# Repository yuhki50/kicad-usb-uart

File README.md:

# USB UART

## Board specifications

* Layer: 2
* Dimensions: 43.5 x 28.5 mm
* PCB Thickness: 1.0 mm
* PCB Color: Green
* Surface Finish: HASL Lead Free
* Castellated Hole: No
* Copper Weight:1oz

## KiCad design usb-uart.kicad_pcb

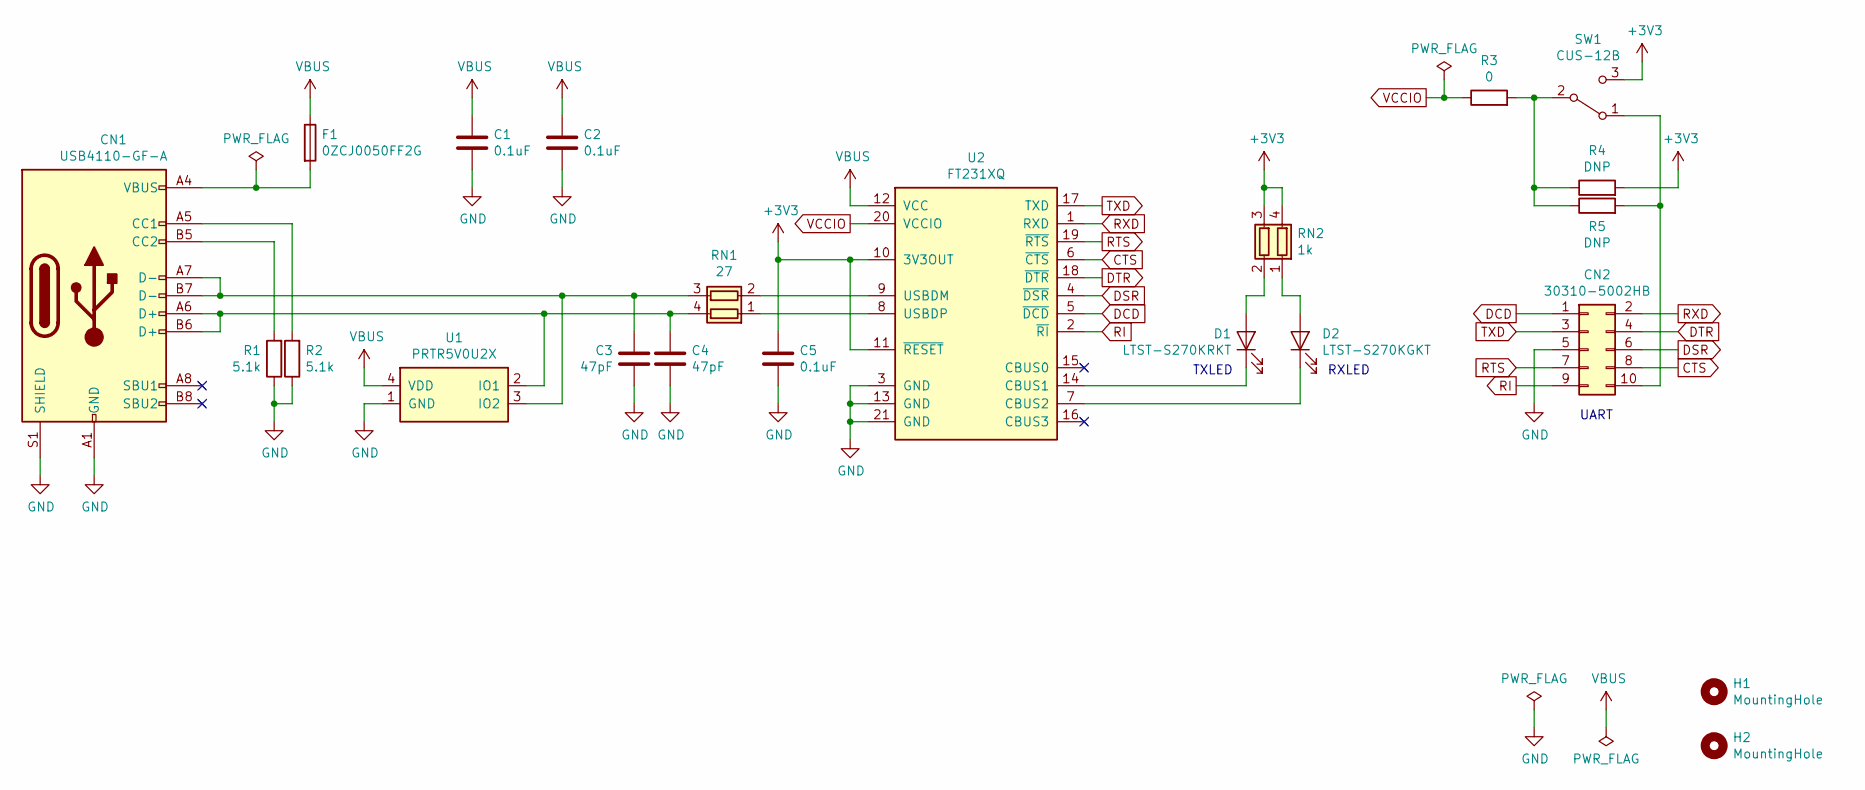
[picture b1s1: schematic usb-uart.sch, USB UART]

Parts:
C1, C2, C5: 0.1uF; C_0402_1005Metric
C3, C4: 47pF; C_0402_1005Metric
CN1: USB4110-GF-A
CN2: 30310-5002HB
D1: LTST-S270KRKT; LED_0603_1608Metric
D2: LTST-S270KGKT; LED_0603_1608Metric
F1: 0ZCJ0050FF2G; Fuse_1206_3216Metric
H1, H2: MountingHole; MountingHole_2.2mm_M2
R1, R2: 5.1k; R_0402_1005Metric
R3: 0; R_0402_1005Metric
R4, R5: DNP; R_0402_1005Metric
RN1: 27; R_Array_Convex_2x0402
RN2: 1k; R_Array_Convex_2x0402
SW1: CUS-12B
U1: PRTR5V0U2X; SOT-143B
U2: FT231XQ; QFN-20-1EP_4x4mm_P0.5mm_EP2.5x2.5mm

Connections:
+3V3: C5.2, R4.2, RN2.3 (R2.2), RN2.4 (R1.2), SW1.3 (C), U2.10 (3V3OUT), U2.11 (~RESET)
CTS: CN2.8, U2.6 (~CTS)
DCD: CN2.1, U2.5 (~DCD)
DSR: CN2.6, U2.4 (~DSR)
DTR: CN2.4, U2.18 (~DTR)
GND: C1.2, C2.2, C3.2, C4.2, C5.1, CN1.A1 (GND), CN1.A12 (GND), CN1.B1 (GND), CN1.B12 (GND), CN1.S1 (SHIELD), CN2.5, R1.1, R2.1, U1.1 (GND), U2.3 (GND), U2.13 (GND), U2.21 (GND)
unnamed: C3.1, CN1.A7 (D-), CN1.B7 (D-), RN1.3 (R2.2), U1.3 (IO2)
unnamed: C4.1, CN1.A6 (D+), CN1.B6 (D+), RN1.4 (R1.2), U1.2 (IO1)
unnamed: CN1.A4 (VBUS), CN1.A9 (VBUS), CN1.B4 (VBUS), CN1.B9 (VBUS), F1.2
unnamed: CN1.A5 (CC1), R2.2
unnamed: CN1.B5 (CC2), R1.2
unnamed: CN2.10, R5.2, SW1.1 (A)
unnamed: D1.1 (K), U2.14 (CBUS1)
unnamed: D1.2 (A), RN2.2 (R2.1)
unnamed: D2.1 (K), U2.7 (CBUS2)
unnamed: D2.2 (A), RN2.1 (R1.1)
unnamed: R3.2, R4.1, R5.1, SW1.2 (B)
unnamed: RN1.1 (R1.1), U2.8 (USBDP)
unnamed: RN1.2 (R2.1), U2.9 (USBDM)
RI: CN2.9, U2.2 (~RI)
RTS: CN2.7, U2.19 (~RTS)
RXD: CN2.2, U2.1 (RXD)
TXD: CN2.3, U2.17 (TXD)
VBUS: C1.1, C2.1, F1.1, U1.4 (VDD), U2.12 (VCC)
VCCIO: R3.1, U2.20 (VCCIO)

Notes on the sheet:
RXLED
TXLED
UART

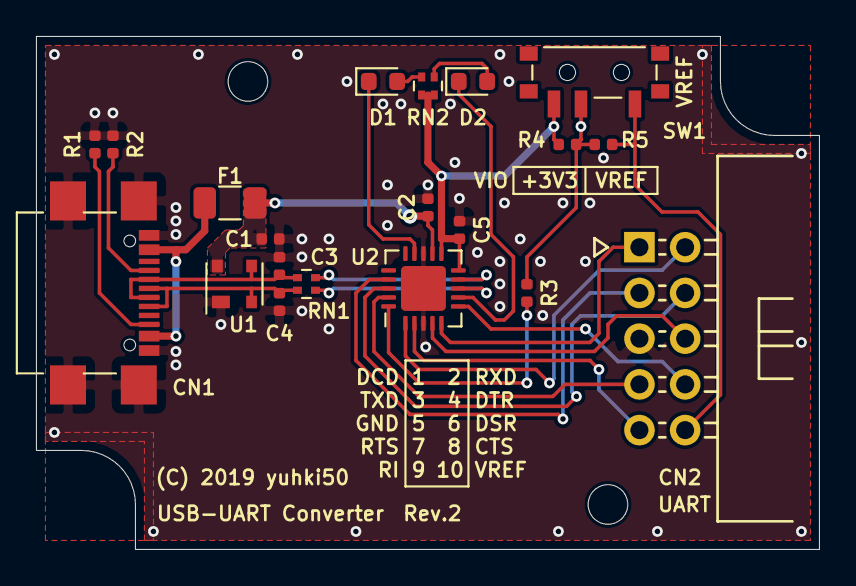
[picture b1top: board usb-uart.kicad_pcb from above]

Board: 2 copper layers, 43.5 x 28.5 mm, 22 parts (0 on the bottom side), 25 nets.

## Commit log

2019-12-07 Add gitignore
2019-12-07 Create project using KiCad (v5.1.5-0-10_14)
2019-12-08 Add library, modules
2019-12-09 Implement
2019-12-09 Add README
2019-12-30 Update
    * USB Type Cのプルアップ抵抗のフットプリントを変更する
    * USB Type Cをより基板から飛び出す
    * R4を未実装にする

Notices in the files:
usb-uart.kicad_pcb:
(C) 2019 yuhki50
